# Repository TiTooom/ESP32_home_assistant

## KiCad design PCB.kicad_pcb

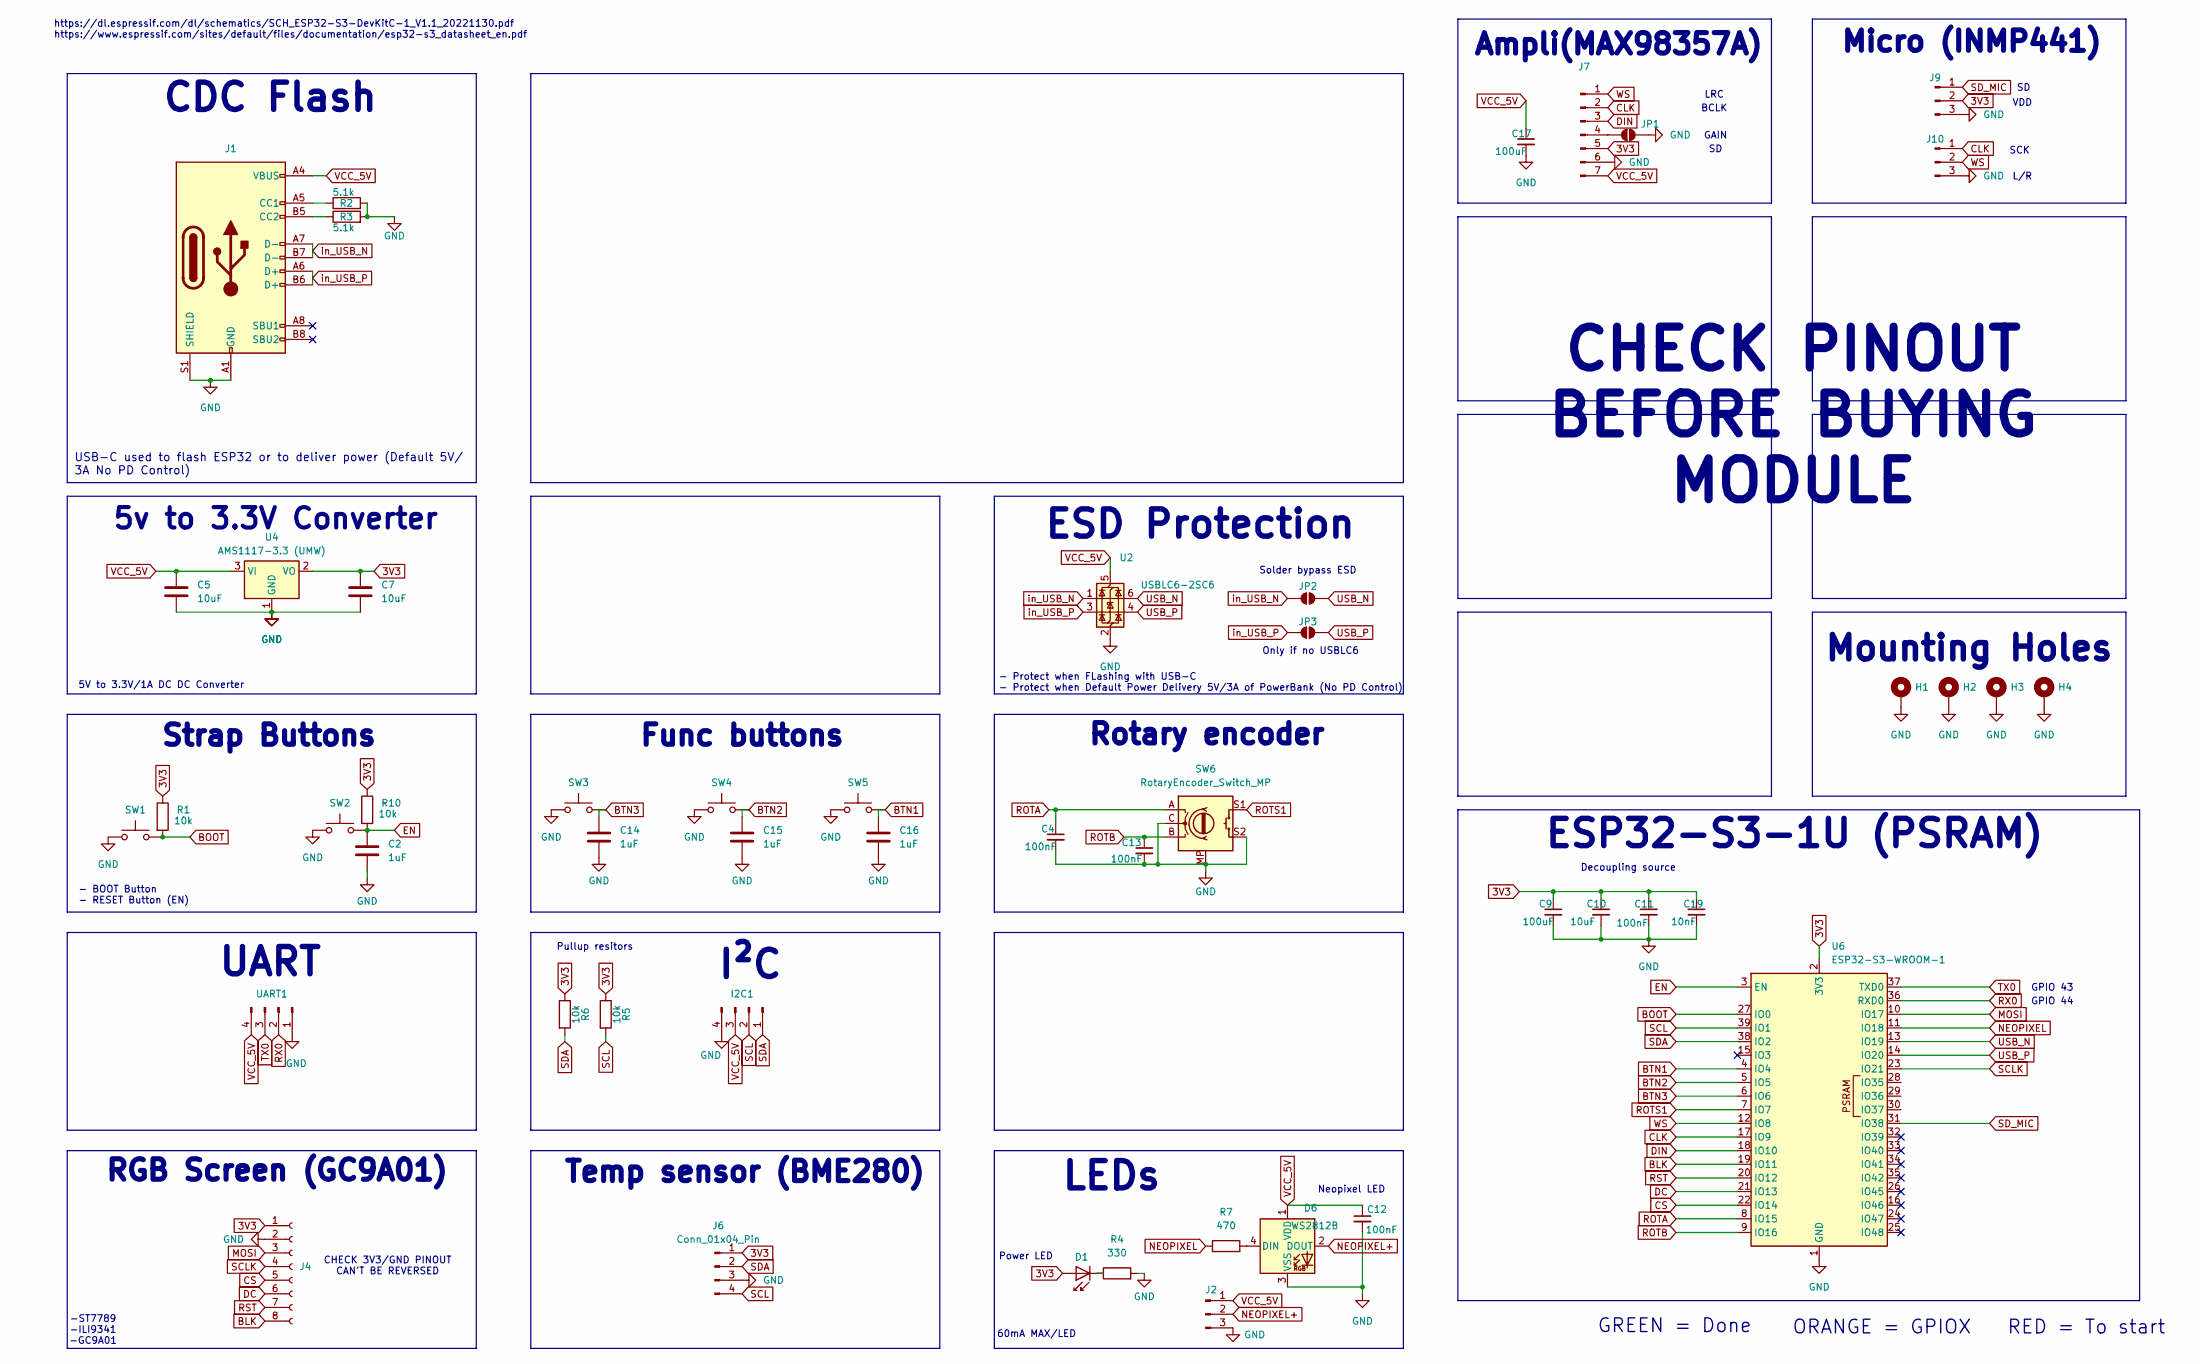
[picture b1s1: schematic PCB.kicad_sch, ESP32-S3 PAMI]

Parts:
C2, C14, C15, C16: 1uF; C_0805_2012Metric_Pad1.18x1.45mm_HandSolder
C4, C11, C12, C13: 100nF; C_0805_2012Metric_Pad1.18x1.45mm_HandSolder
C5, C7: 10uF; C_1206_3216Metric_Pad1.33x1.80mm_HandSolder
C9, C17: 100uF; C_1210_3225Metric_Pad1.33x2.70mm_HandSolder
C10: 10uF; C_0805_2012Metric_Pad1.18x1.45mm_HandSolder
C19: 10nF; C_0805_2012Metric_Pad1.18x1.45mm_HandSolder
D1: LED_0805_2012Metric_Pad1.15x1.40mm_HandSolder
D6: WS2812B; LED_WS2812B_PLCC4_5.0x5.0mm_P3.2mm
H1, H2, H3, H4: MountingHole_Pad; MountingHole_3.2mm_M3_Pad
I2C1: Conn_01x04_Pin; PinSocket_1x04_P2.54mm_Vertical
J1: USB_C_Receptacle_USB2.0_16P; USB_C_Receptacle_HRO_TYPE-C-31-M-12
J2, J9, J10: Conn_01x03_Pin; PinHeader_1x03_P2.54mm_Vertical
J4: Conn_01x08_Socket; PinSocket_1x08_P2.54mm_Vertical
J6: Conn_01x04_Pin; PinHeader_1x04_P2.54mm_Vertical
J7: Conn_01x07_Pin; PinHeader_1x07_P2.54mm_Vertical
JP1: SolderJumper_2_Open; SolderJumper-2_P1.3mm_Open_TrianglePad1.0x1.5mm
JP2, JP3: SolderJumper_2_Open; SolderJumper-2_P1.3mm_Open_RoundedPad1.0x1.5mm
R1, R5, R6, R10: 10k; R_1206_3216Metric_Pad1.30x1.75mm_HandSolder
R2, R3: 5.1k; R_0805_2012Metric_Pad1.20x1.40mm_HandSolder
R4: 330; R_0805_2012Metric_Pad1.20x1.40mm_HandSolder
R7: 470; R_0805_2012Metric_Pad1.20x1.40mm_HandSolder
SW1, SW2, SW3, SW4, SW5: SW_Push; SW_Push_SPST_NO_Alps_SKRK
SW6: RotaryEncoder_Switch_MP; RotaryEncoder_Alps_EC11E-Switch_Vertical_H20mm_CircularMoun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
U2: USBLC6-2SC6; SOT-23-6_Handsoldering
U4: AMS1117-3.3 (UMW); SOT-223-3_TabPin2
U6: ESP32-S3-WROOM-1; ESP32-S3-WROOM-1U
UART1: Conn_01x04_Pin; PinHeader_1x04_P2.54mm_Vertical

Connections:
3V3: C7.1, C9.1, C10.1, C11.1, C19.1, D1.2 (A), J4.1, J6.1, J7.5, J9.2, R1.1, R5.1, R6.1, R10.1, U4.2 (VO), U6.2 (3V3)
BLK: J4.8, U6.19 (IO11)
BOOT: R1.2, SW1.2, U6.27 (IO0)
BTN1: C16.1, SW5.2, U6.4 (IO4)
BTN2: C15.1, SW4.2, U6.5 (IO5)
BTN3: C14.1, SW3.2, U6.6 (IO6)
CLK: J7.2, J10.1, U6.17 (IO9)
CS: J4.5, U6.22 (IO14)
DC: J4.6, U6.21 (IO13)
DIN: J7.3, U6.18 (IO10)
EN: C2.1, R10.2, SW2.2, U6.3 (EN)
GND: C2.2, C4.2, C5.2, C7.2, C9.2, C10.2, C11.2, C12.2, C13.2, C14.2, C15.2, C16.2, C17.2, C19.2, D6.3 (VSS), H1.1, H2.1, H3.1, H4.1, I2C1.4, J1.A1 (GND), J1.A12 (GND), J1.B1 (GND), J1.B12 (GND), J1.S1 (SHIELD), J2.3, J4.2, J6.3, J7.6, J9.3, J10.3, JP1.2 (B), R2.2, R3.2, R4.2, SW1.1, SW2.1, SW3.1, SW4.1, SW5.1, SW6.C, SW6.MP, SW6.S2, U2.2 (GND), U4.1 (GND), U6.1 (GND), U6.40 (GND), U6.41 (GND), UART1.1; also elsewhere on the board
MOSI: J4.3, U6.10 (IO17)
NEOPIXEL: R7.1, U6.11 (IO18)
NEOPIXEL+: D6.2 (DOUT), J2.2
unnamed: D1.1 (K), R4.1
unnamed: D6.4 (DIN), R7.2
unnamed: J1.A5 (CC1), R2.1
unnamed: J1.B5 (CC2), R3.1
unnamed: J7.4, JP1.1 (A)
ROTA: C4.1, SW6.A, U6.8 (IO15)
ROTB: C13.1, SW6.B, U6.9 (IO16)
ROTS1: SW6.S1, U6.7 (IO7)
RST: J4.7, U6.20 (IO12)
RX0: U6.36 (RXD0), UART1.2
SCL: I2C1.2, J6.4, R5.2, U6.39 (IO1)
SCLK: J4.4, U6.23 (IO21)
SDA: I2C1.1, J6.2, R6.2, U6.38 (IO2)
SD_MIC: J9.1, U6.31 (IO38)
TX0: U6.37 (TXD0), UART1.3
USB_N: JP2.2 (B), U2.6 (I/O1), U6.13 (IO19)
USB_P: JP3.2 (B), U2.4 (I/O2), U6.14 (IO20)
VCC_5V: C5.1, C12.1, C17.1, D6.1 (VDD), I2C1.3, J1.A4 (VBUS), J1.A9 (VBUS), J1.B4 (VBUS), J1.B9 (VBUS), J2.1, J7.7, U2.5 (VBUS), U4.3 (VI), UART1.4; also elsewhere on the board
WS: J7.1, J10.2, U6.12 (IO8)
in_USB_N: J1.A7 (D-), J1.B7 (D-), JP2.1 (A), U2.1 (I/O1)
in_USB_P: J1.A6 (D+), J1.B6 (D+), JP3.1 (A), U2.3 (I/O2)

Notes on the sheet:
USB-C used to flash ESP32 or to deliver power (Default 5V/ 3A No PD Control)
LEDs
Decoupling source
VDD
Temp sensor (BME280)
Solder bypass ESD
CHECK 3V3/GND PINOUT CAN'T BE REVERSED
Func buttons
GAIN
GREEN = Done
ESP32-S3-1U (PSRAM)
Only if no USBLC6
RGB Screen (GC9A01)
RED = To start
ESD Protection
CHECK PINOUT BEFORE BUYING MODULE
CDC Flash
https://www.espressif.com/sites/default/files/documentation/esp32-s3_datasheet_en.pdf
GPIO 44
Mounting Holes
60mA MAX/LED
-ST7789 -ILI9341 -GC9A01
GPIO 43
I²C
ORANGE = GPIOX
Strap Buttons
LRC
- Protect when FLashing with USB-C - Protect when Default Power Delivery 5V/3A of PowerBank (No PD Control)
L/R
- BOOT Button - RESET Button (EN)
UART
https://dl.espressif.com/dl/schematics/SCH_ESP32-S3-DevKitC-1_V1.1_20221130.pdf
5V to 3.3V/1A DC DC Converter
Micro (INMP441)
SCK
BCLK
Power LED
5v to 3.3V Converter
Ampli(MAX98357A)
Rotary encoder

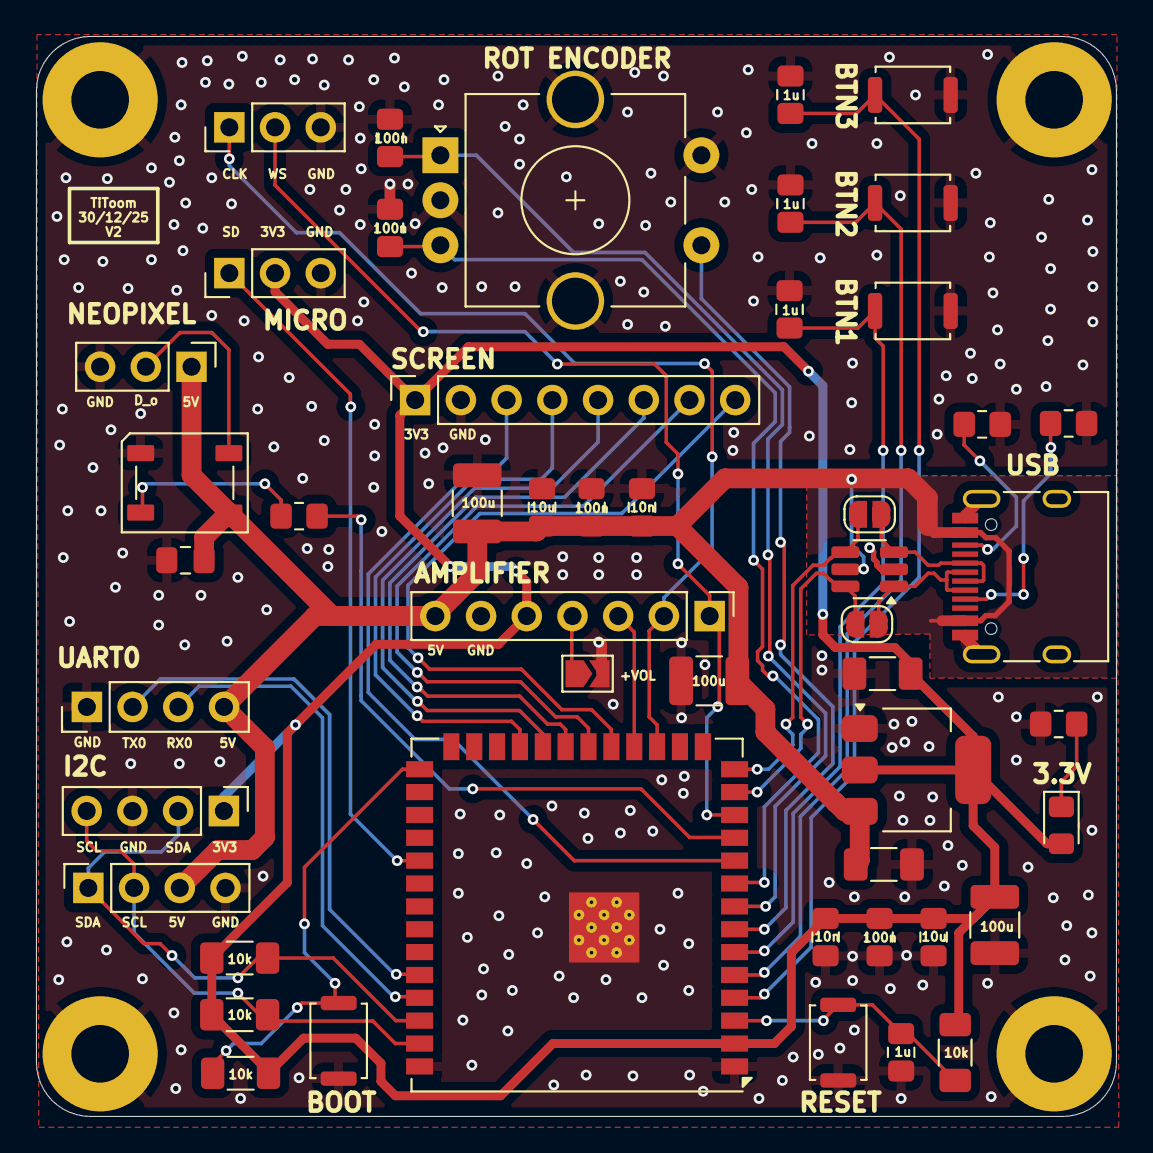
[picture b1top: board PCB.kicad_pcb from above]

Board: 2 copper layers, 60.0 x 60.0 mm, 53 parts (0 on the bottom side), 36 nets.

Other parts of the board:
C3: 10uF; C_0805_2012Metric_Pad1.18x1.45mm_HandSolder
C6: 100nF; C_0805_2012Metric_Pad1.18x1.45mm_HandSolder
C8: 10nF; C_0805_2012Metric_Pad1.18x1.45mm_HandSolder
C18: 100uF; C_1210_3225Metric_Pad1.33x2.70mm_HandSolder

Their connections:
GND: C3.2, C6.2, C8.2, C18.2; also elsewhere on the board
VCC_5V: C3.1, C6.1, C8.1, C18.1; also elsewhere on the board

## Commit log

2025-12-09 debut rootage
2025-12-11 fin routage
2025-12-12 test DRC
2025-12-12 fin V1
2025-12-30 dernier upload V1
2025-12-31 update V2
